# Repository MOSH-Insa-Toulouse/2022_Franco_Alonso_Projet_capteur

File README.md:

# 2022_Franco_Alonso_Projet_capteur

Ce repository Git contient les ressources nécessaire pour le projet 2022 qui s'inscrit dans l'UF *"Du capteur au banc de Test"* de l'INSA de Toulouse, 4ème année de Génie Physique.

---
## Sommaire

- [2022_Franco_Alonso_Projet_capteur](#2022_franco_alonso_projet_capteur)
  - [Sommaire](#sommaire)
  - [1) Livrables](#1-livrables)
  - [2) Description](#2-description)
  - [3) Shield PCB](#3-shield-pcb)
  - [4) Arduino](#4-arduino)
  - [5) Application Android APK](#5-application-android-apk)
    - [5.1) MIT App inventor](#51-mit-app-inventor)
    - [5.2) Notre application](#52-notre-application)
  - [6) Banc de test](#6-banc-de-test)
    - [6.1) Rayon de courbure](#61-rayon-de-courbure)
    - [6.2) Répétabilité](#62-répétabilité)
  - [7) Datasheet](#7-datasheet)
  - [8) Information sur les auteurs](#8-information-sur-les-auteurs)

---
## 1) Livrables

- Shield PCB réalisé avec KiCad
- Code Arduino permettant la mesure de la resistance et de la tension du capteur, ainsi que le contrôle d'un module Bluetooth, d'un écran OLED et d'un encodeur rotatoire
- Application android APK réalisée avec MIT APP INVENTOR
- Protocole et code Arduino du Banc de test
- Datasheet du capteur de déformation

---
## 2) Description

Dans le cadre de l'UF MOSH, nous avons conçu un capteur résistif composé de matériaux peu chers : un simple papier et un crayon suffisent à créer ce capteur.

Ici, le phénomène physique observé est l'effet tunnel. En effet, il existe un lien entre la conduction des électrons et la distance interatomique du réseau percolet. En faisant varier la distance séparant les particules du réseau (en pliant une feuille de papier sur laquelle on aura déposé du graphite par exemple), la conductivité du graphite varie, la résistivité varie également, et donc, la résistance variera aussi en fonction des dimensions du capteur. C'est cette propriété que l'on va exploiter afin de créer notre capteur résistif.  

Nous avons également implémenté  un shield sur notre chaine de mesures. Ce dernier a été conçu a l'aide du logiciel KICAD et aura un rôle de conditionneur du signal. Le shield est composé d'un amplificateur transimpédance, d'un module Bluetooth, d'un écran OLED, d'un encodeur rotatoire ainsi que d'une entrée analogique pour le capteur résistif.  

Pour finir, nous avons effectué l'ensemble des tests du circuit sur le logiciel LTSpice (voir [_Rapport LTSpice_](https://github.com/MOSH-Insa-Toulouse/2022_Franco_Alonso_Projet_capteur/blob/8504636d878c9423babecade3b70e7a892836c6b/Rapport_LTSpice.pdf)).  

Nous avons ensuite imprimé notre circuit PCB après validation de l'équipe pédagogique.  

Puis, nous avons utilisé une carte Arduino pour la lecture des mesures et la création des fonctions relatives à l'écran OLED, au module Bluetooth ainsi qu'a l'encodeur rotatoire.  

Ensuite, avec le site MIT App Inventor, nous avons développé une application Android qui a pour but de recevoir des données via Bluetooth.  

Et enfin, nous avons réalisé notre propre banc de test : nous avons effectué un test de rayon de courbure et un test de répétabilité avec deux types de crayons (B, HB).  

---
## 3) Shield PCB

Sur le logiciel KICAD nous avons créé des modèles pour l'amplificateur transimpédance, le module Bluetooth, l'écran OLED et l'encodeur rotatoire. Nous avons ensuite créé ou assigné des empreintes à chaque composante du circuit électronique (amplificateur, Bluetooth, OLED, encodeur rotatoire mais aussi résitances et capacités). Puis, nous avons tracé le chevelu du PCB et enfin nous avons modélisé notre PCB en 3D pour vérifier qu'aucun élément ne se superpose et qu'il n'y aura pas de problème lors de la réalisation du PCB.  

Schéma du circuit électrique sur LTSpice:  

Schématique de l'amplificateur opérationel LTC1050:  

Schématique du module Bluetooth HC-05:  

Schématique de l'écran OLED:  

Schématique de l'encodeur rotatoire KY-040:  

Schématique des pins de la carte Arduino:  

Schématique du circuit amplificateur transimpédance:  

Empreinte de l'amplificateur opérationel LTC1050:  

Empreinte du module Bluetooth HC-05:  

Empreinte de l'écran OLED:  

Empreinte de l'encodeur rotatoir KY-040:  

Empreinte du PCB en entier:  

Modélisation 3D du PCB:  

---
## 4) Arduino

Voici notre code Arduino qui permet de :

- mesurer la tension en sortie du circuit transimpédance
- calculer la résistance correspondante du capteur grâce à la tension mesurée (fonction de transfert)
- visualiser ces valeurs (tension et résistance) dans le moniteur série
- afficher ces deux valeurs (tension et résistance) sur l'écran OLED
- envoyer les valeurs de résistance par Bluetooth à l'application APK
- utiliser un encodeur rotatoire pour choisir d'afficher sur l'écran OLED et d'envoyer par Bluetooth les valeurs de résistance en Ω, kΩ ou MΩ  

```
// Pour le Bluetooth
#include <SoftwareSerial.h>
#include <Arduino.h>
#include <string.h>
#define rxPin 11 //Broche 11 en tant que RX, à raccorder sur TX du HC-05
#define txPin 10 //Broche 10 en tant que TX, à raccorder sur RX du HC-05
#define baudrate 9600
#define encoder0PinA  2  //CLK Output A Do not use other pin for clock as we are using interrupt
#define encoder0PinB  3  //DT Output B
#define Switch 5 // Switch connection if available
int value;
int rotation;
int RotPosition = 0;
boolean LeftRight;
float Rs2=0;
volatile unsigned int encoder0Pos = 0;
SoftwareSerial mySerial(rxPin ,txPin); //Définition du software serial

float Vadc;

// Pour le OLED
#include <Adafruit_SSD1306.h>

#define nombreDePixelsEnLargeur 128         // Taille de l'écran OLED, en pixel, au niveau de sa largeur
#define nombreDePixelsEnHauteur 64          // Taille de l'écran OLED, en pixel, au niveau de sa hauteur
#define brocheResetOLED         -1          // Reset de l'OLED partagé avec l'Arduino (d'où la valeur à -1, et non un numéro de pin)
#define adresseI2CecranOLED     0x3C        // Adresse de "mon" écran OLED sur le bus i2c (généralement égal à 0x3C ou 0x3D)

Adafruit_SSD1306 ecranOLED(nombreDePixelsEnLargeur, nombreDePixelsEnHauteur, &Wire, brocheResetOLED);

/////////////////////////////////////////////////////////////////////////////////////////////////////////////////////////////////////////////////////////////////////////

void Affichage_OLED(float Rs, float Vadc){ 
  byte tailleDeCaractere=2;
  byte numeroDeLigne=1;
  boolean bCouleurInverse = false;
  ecranOLED.clearDisplay();                                   // Effaçage de l'intégralité du buffer
  ecranOLED.setTextSize(tailleDeCaractere);                   // Taille des caractères (1:1, puis 2:1, puis 3:1)
  ecranOLED.setCursor(0, 0);                                  // Déplacement du curseur en position (0,0), c'est à dire dans l'angle supérieur gauche
  ecranOLED.setTextColor(SSD1306_WHITE);                  // Affichage du texte en "blanc" (avec la couleur principale, en fait, car l'écran monochrome peut être coloré)
  ecranOLED.print("V= ");
  ecranOLED.print(Vadc);
  ecranOLED.println(" V");
  ecranOLED.print("R= ");
  ecranOLED.print(Rs);
  bCouleurInverse = !bCouleurInverse;
  ecranOLED.display();                            // Transfert le buffer à l'écran

  // ***********************************************************************
  // Affichage de 8 lignes à couleurs alternées, dans chaque écran successif
  // ***********************************************************************
  
  /*if(bCouleurInverse)
    ecranOLED.setTextColor(SSD1306_BLACK, SSD1306_WHITE);   // Couleur du texte, et couleur du fond
  else
    
  delay(500);*/
}

/////////////////////////////////////////////////////////////////////////////////////////////////////////////////////////////////////////////////////////////////////////

double Rs;
int Vcc=5;
int R1=100000;
int R3=100000;
int R5=10000;
int R2=1000;

void Bluetooth_write(double Rs){
  double Res = Rs;
  mySerial.println(Res);
  delay(500);
}

/////////////////////////////////////////////////////////////////////////////////////////////////////////////////////////////////////////////////////////////////////////

void mesure(){
  // read the input on analog pin 0:
  double  sensorValue = analogRead(A0);         //on divise par 4 pour être sur une plage de 256 et non une plage de 1024 car l'analogRead donne une valeur entre 0 et 1023
  
  // Convert the analog reading (which goes from 0 - 1023) to a voltage (0 - 5V):
  Vadc = sensorValue * (Vcc / 1023.0);
 
  Rs = ((1+R3/R2)*R1*(1023/Vadc))-R1-R5;
  //Serial.println(Vadc); 
}

// on voit sur le moniteur que Rs varie entre 35000 et 15M environ

/////////////////////////////////////////////////////////////////////////////////////////////////////////////////////////////////////////////////////////////////////////

void setup() {
  Serial.begin(9600);
  pinMode(rxPin,INPUT);
  pinMode(txPin,OUTPUT);
  mySerial.begin(9600);
  ecranOLED.begin(SSD1306_SWITCHCAPVCC, adresseI2CecranOLED);
  pinMode(encoder0PinA, INPUT); 
  digitalWrite(encoder0PinA, HIGH);       // turn on pullup resistor
  pinMode(encoder0PinB, INPUT); 
  digitalWrite(encoder0PinB, HIGH);       // turn on pullup resistor
  rotation = digitalRead(encoder0PinA); 
}

void loop() {
 value = digitalRead(encoder0PinA);
     if (value != rotation){ // we use the DT pin to find out which way we are turning.
     if (digitalRead(encoder0PinB) != value) {  // Clockwise
       RotPosition ++; 
       if (RotPosition==3){
        RotPosition=0;
       }
     } else { //Counterclockwise
       RotPosition--;
       if (RotPosition==-3){
        RotPosition=0;
       }
     }
     rotation = value;
     }
    mesure();
      if (RotPosition==-1){
        //mesure();
        Rs=Rs/1000;
        Bluetooth_write(Rs);  
        Affichage_OLED(Rs, Vadc);
        //Serial.println(Rs);
        ecranOLED.println(" k");
        ecranOLED.display();
     }
      else if (RotPosition==-2){
        //mesure();
        //Serial.println(Rs/1000000);
        Bluetooth_write(Rs/1000000);
        Affichage_OLED(Rs/1000000, Vadc);
        ecranOLED.println(" M");
        ecranOLED.display();
     }
     else if (RotPosition==0){
        //Serial.println(Rs);
      Bluetooth_write(Rs);
      Affichage_OLED(Rs, Vadc); 
     }
      else if (RotPosition==1){
        //mesure();
        Rs=Rs/1000;
        Bluetooth_write(Rs);  
        Affichage_OLED(Rs, Vadc);
        //Serial.println(Rs);
        ecranOLED.println(" k");
        ecranOLED.display();
     }
      else if (RotPosition==2){
        //mesure();
       // Serial.println(Rs/1000000);
        Bluetooth_write(Rs/1000000);
        Affichage_OLED(Rs/1000000, Vadc);
        ecranOLED.println(" M");
        ecranOLED.display();
     }
     else{
      //mesure();
      //Serial.println(Rs);
      Bluetooth_write(Rs);
      Affichage_OLED(Rs, Vadc);  
     }
     //Serial.print("Encoder RotPosition: ");
     //Serial.println(RotPosition);
     
     Serial.println(Rs);
     //Serial.println(Vadc);
     // this will print in the serial monitor.  
}
```

---
## 5) Application Android APK

L'application android développée sur MIT App Inventor sert à:

- Récupérer la valeur de la résistance du capteur graphite (calculée par le code Arduino à partir de la tension mesurée)
- Afficher cette valeur de résistance
- Tracer un graphique qui décrit l'évolution de la résistance du capteur en fonction du temps

### 5.1) MIT App inventor

Le site internet de création d'application [_MIT App Inventor_](https://appinventor.mit.edu/)

### 5.2) Notre application

Interface de l'application sur un smartphone :  

Schéma en block du code de l'application :  

Toutefois, notre application est perfectible. Il lui arrive d'avoir des erreurs obligeant l'application à se fermer, notamment lorsque le smartphone reçoit des valeurs infinies.  

---
## 6) Banc de test

### 6.1) Rayon de courbure

Nous avons effectué différents tests pour étudier l'influence du rayon de courbure sur la résistance de notre capteur. Pour cela, nous avons créé un banc de test "low-cost" en prenant différents objets cylindriques présents dans la salle d'instrumentation du Génie Physique (GP).

Puis, nous avons enroulé notre capteur autour de ces objets cylindriques dans un sens comme dans l'autre (extension/compression) et mesuré les variations de résistance pour les crayons de type B et de type HB.
Nous avons alors tracé deux graphes avec leurs courbes de tendance:  

### 6.2) Répétabilité

Ici, nous avons voulu mesurer la répétabilité de notre capteur, c'est-à-dire, à partir de combien de mesures notre capteur n'est plus fiable.
Pour y arriver, nous avons créé notre propre banc de test à partir d'un servo-moteur (et son code Arduino), de scotch, de carton et d'un support en rigide. Nous avons agrandi l'aile fixé au servo-moteur grâce à un morceau de carton et nous avons scotché ce servo-moteur à un support rigide que nous avons lui même scotché sur le bord d'un meuble. En ce qui concerne le capteur, nous avons scotché un support rigide sur le bord du même meuble à une petite distance de notre servo-moteur, ce qui nous a permis de positionner les pinces métalliques et notre capteur face à l'aile du servo-moteur qui va effectuer des aller-retours pour que le capteur subisse des cycles d'extension/compression (voir [_Vidéo test de répétabilité_](https://github.com/MOSH-Insa-Toulouse/2022_Franco_Alonso_Projet_capteur/blob/469d8a52910f487a39b89d7652cd1226eb0d3d92/Images/Test_Repetabilite_video.mp4)).  

Après des mesures pour des crayons de type B et des crayons de type HB, nous avons obtenu deux courbes représentant l'évolution de la résistance mesurée par le capteur en fonction du nombre de cyles d'extension/compression effectués.  

Code Arduino du servo-moteur:  

```
// Sweep by BARRAGAN
#include <Servo.h>

Servo myservo;  // create servo object to control a servo
                // a maximum of eight servo objects can be created

int pos = 0;    // variable to store the servo position

void setup()
{
  Serial.begin(9600);
  myservo.attach(9);  // attaches the servo on pin 9 to the servo object
}

void loop()
{
  for(pos = 30; pos <= 150; pos += 1)  // goes from 30 degrees to 150 degrees
  {                                  // in steps of 1 degree
    myservo.write(pos);              // tell servo to go to position in variable 'pos'
    Serial.println(pos);
    delay(5);                       // waits 5ms for the servo to reach the position
  }
  for(pos = 150; pos>=31; pos-=1)     // goes from 150 degrees to 30 degrees
  {                                
    myservo.write(pos);              // tell servo to go to position in variable 'pos'
    Serial.println(pos);
    delay(5);                       // waits 5ms for the servo to reach the position
  }
} 
```

---
## 7) Datasheet

Datasheet en format pdf à télécharger [_ici_](https://github.com/MOSH-Insa-Toulouse/2022_Franco_Alonso_Projet_capteur/blob/540ff39c7f5d5399cfc770728529d42a2bad8d82/Datasheet/Datasheet_Capteur_papier.pdf).

---
## 8) Information sur les auteurs

Edouard FRANCO / Pablo ALONSO RODRIGUEZ

- edouard.franco@free.fr
- pablo.alonsorgz@gmail.com

Étudiants à l'INSA de Toulouse en 4ème année Génie Physique

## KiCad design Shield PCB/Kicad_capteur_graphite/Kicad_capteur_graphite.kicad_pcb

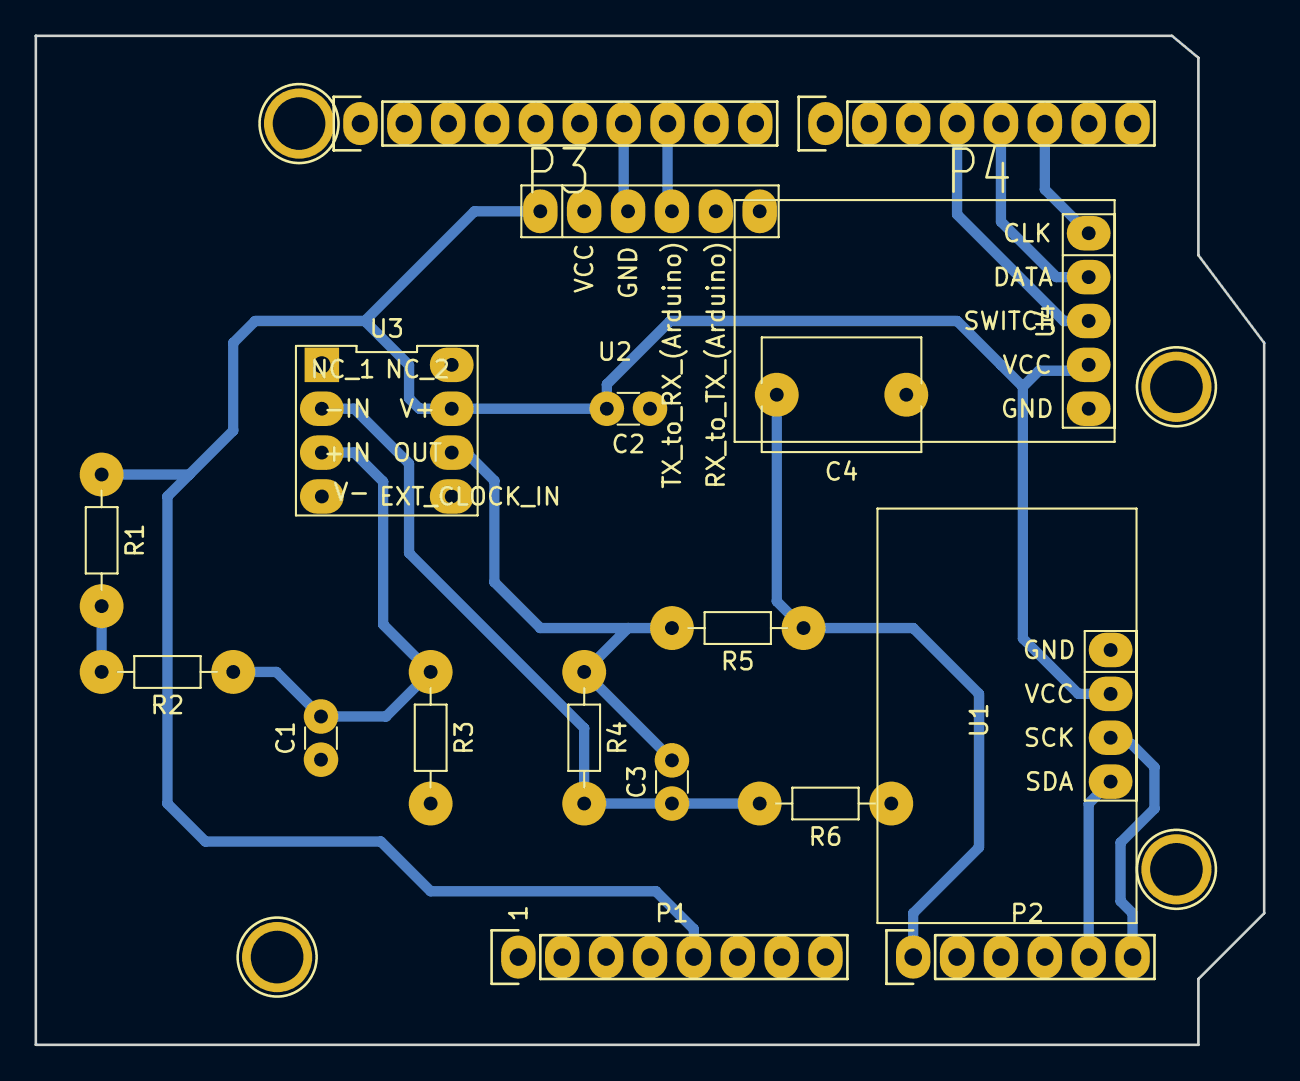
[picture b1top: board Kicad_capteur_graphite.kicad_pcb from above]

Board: 2 copper layers, 71.1 x 58.4 mm, 22 parts (0 on the bottom side), 14 nets.

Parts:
C1, C2, C3: 100n; C_Disc_D3.0mm_W1.6mm_P2.50mm
C4: 100n; C_Rect_L9.0mm_W6.4mm_P7.50mm_MKT
P1: Power; Socket_Strip_Arduino_1x08
P2: Analog; Socket_Strip_Arduino_1x06
P3: Digital; Socket_Strip_Arduino_1x10
P4: Digital; Socket_Strip_Arduino_1x08
P5, P6, P7, P8: CONN_01X01; Arduino_1pin
R1: Rsensor; R_Axial_DIN0204_L3.6mm_D1.6mm_P7.62mm_Horizontal
R2: 10k; R_Axial_DIN0204_L3.6mm_D1.6mm_P7.62mm_Horizontal
R3, R4: 100k; R_Axial_DIN0204_L3.6mm_D1.6mm_P7.62mm_Horizontal
R5, R6: 1k; R_Axial_DIN0204_L3.6mm_D1.6mm_P7.62mm_Horizontal
U1: OLED_0.91; OLED
U2: Bluetooth-HC05; BLUETOOTH_HC05
U3: LTC1050
U4: KY-040; KY_040

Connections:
+5V: C2.2, P1.5, R1.1, U1.2, U2.1, U3.7, U4.4
ADC: C4.2, P2.1, R5.1
CLK: P4.6, U4.1
DATA: P4.5, U4.2
GND: C1.1, C2.1, C4.1, P1.6, P1.7, P3.4, R3.2, R6.1, U1.1, U2.2, U3.4, U4.5
IN+: C1.2, R2.1, R3.1, U3.3
IN-: C3.1, R4.2, R6.2, U3.2
unnamed: C3.2, R4.1, R5.2, U3.6
unnamed: R1.2, R2.2
RX: P3.7, U2.3
SCK: P2.6, U1.3
SDA: P2.5, U1.4
SWITCH: P4.4, U4.3
TX: P3.8, U2.4

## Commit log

2022-04-12 update README v1
2022-04-12 AJOUT Kicad
2022-04-16 captures d'écran
2022-04-23 Datasheet
2022-04-23 Shield PCB
2022-04-23 Arduino
2022-04-23 Banc de test
2022-04-23 rayon de courbure
2022-05-01 présentation
2022-05-13 APK + Arduino
